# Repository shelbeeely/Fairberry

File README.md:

# Fairberry (e-ink fork)

This is a personal fork of [Dakkaron/Fairberry](https://github.com/Dakkaron/Fairberry), which adds a detachable BlackBerry Q10 keyboard to phones, physically clamped on and wired over USB. If you want that original phone-focused project, go there instead — this fork has moved away from it.

**The direction here now: a standalone, battery-powered BlackBerry-style device -- Q10 keyboard, a five-way trackball, a mic and speaker, microSD storage -- that pairs *wirelessly* with the [Xteink X4](https://www.xteink.com/products/xteink-x4) (or any BLE HID host) instead of physically attaching to it.** No separate battery / host-powered-only was the original project's whole philosophy; this fork has deliberately dropped that in favor of its own LiPo battery and its own enclosure, built primarily for e-ink devices running the [Free Ink SDK](https://freeink.org/) but not exclusive to them -- anything that speaks BLE HID keyboard is a valid target.

See [Hardware_Standalone_Smart_Keyboard.md](Documentation/Hardware_Standalone_Smart_Keyboard.md) for the current primary build. Two earlier, simpler stages are still in the repo and still valid if you want something less involved:
1. [Hardware_Fairberry_Mainboard.md](Documentation/Hardware_Fairberry_Mainboard.md) -- the original USB/BLE keyboard-only mainboard.
2. [Hardware_ESP32_Trackball_Mainboard.md](Documentation/Hardware_ESP32_Trackball_Mainboard.md) -- adds the trackball, still host-powered, classic ESP32.

The standalone smart keyboard supersedes both for pairing with the X4 specifically, but they're simpler builds if you don't want the battery/mic/speaker/SD/WiFi scope.

## Writer deck: four components, one repo

The keyboard alone is one half of the picture. Combined with an X4 running a FreeInk-SDK writer app, this becomes a full distraction-free writing device -- a "writer deck," in the vein of a Freewrite or AlphaSmart, built from this project's own parts. Four separate-but-interlinked pieces, all in this repo:

| Component | Directory | What it is |
|---|---|---|
| Keyboard firmware | [`BBQ10/`](BBQ10) | The physical keyboard + trackball + voice typing, BLE HID |
| X4 firmware | [`X4Firmware/`](X4Firmware) | The writer app (library + editor screens) running on the X4 |
| Hardware | [`KiCad/`](KiCad), [`Case/`](Case) | PCB design, 3D-printable case |
| Web GUI | [`WebGUI/`](WebGUI) | The keyboard-hosted local browser dashboard (implementation lives in `BBQ10/web_server.h`) |

Start with [Hardware_X4_Writer_Deck.md](Documentation/Hardware_X4_Writer_Deck.md) for how the pieces fit together -- it's also the most honestly unproven part of this repo (see its Status section: I read FreeInk SDK's docs site, but never had the actual SDK source or hardware in front of me to compile/test against, unlike the keyboard firmware).

## Status / known limitation

Good news on the software side: FreeInk SDK has a purpose-built BLE keyboard host — [`BleKeyboardHost`](https://freeink.org/docs/lib-ble) (the `lib-ble` library). Per its docs, it's a real BLE HID **host** (central role) that explicitly supports "keyboards, page turners, remote buttons and similar devices that expose the HID service" — not just page-turner remotes as I originally assumed here. It works on both ESP32-C3 and ESP32-S3 (BLE only, no Bluetooth Classic), which covers the plain X4 (C3) as well as the X4 Classic/Pro (S3). Pairing defaults to "Just Works" (no passkey needed), which is what a keyboard-only peripheral like Fairberry's `BOARD_TYPE ESP32` needs.

The catch: it's an **opt-in capability**, gated behind the `FREEINK_CAP_BLE_HID_HOST` build flag (off by default) plus adding the NimBLE stack as a dependency. So the real question isn't "does the ecosystem support external keyboards" (it does) — it's "does the specific firmware image flashed on your X4 have that flag turned on." Stock/vendor Xteink firmware almost certainly doesn't.

Checked directly against [freeink-sdk's `platformio.sample.ini`](https://github.com/Free-Ink/freeink-sdk/blob/main/platformio.sample.ini): the stock `[env:xteink_x4]` build env is just

```ini
[env:xteink_x4]
extends = base
board = esp32-c3-devkitm-1
build_flags =
  ${base.build_flags}
  -DFREEINK_DEVICE_X4=1
```

— no BLE HID host flag. Building a FreeInk-SDK firmware for the X4 that can actually pair with a Fairberry keyboard means adding, at minimum:

```ini
build_flags =
  ${base.build_flags}
  -DFREEINK_DEVICE_X4=1
  -DFREEINK_CAP_BLE_HID_HOST=1
lib_deps =
  ${base.lib_deps}
  h2zero/NimBLE-Arduino@^2.3.8
```

to your own build, then flashing that instead of whatever firmware is on the device now.

I have **not yet confirmed** this end-to-end against a physical X4 — that's the next step. I also haven't found documented USB HID host support in FreeInk SDK for any target, so the USB-attached Fairberry board types (`FAIRBERRY_V0_3_0`, `ARDUINO`) are more speculative than the BLE path right now; BLE (`BOARD_TYPE ESP32`) is the one with an actual matching host-side API to target.

## What can you expect?

Everything from the upstream project still applies at the electronics level: same BBQ10 keyboard, same mainboard, same firmware, same key combos (cursor mode, sticky modifiers, dead keys, backlight controls — see [UX_Shortcuts_and_Apps.md](Documentation/UX_Shortcuts_and_Apps.md)). What's changing here is the case/mount and the target device.

Demo video of the original phone version: 

## How to build it?

**Standalone smart keyboard (primary build)**: `BOARD_TYPE FAIRBERRY_ESP32S3_SMART` on an ESP32-S3. See [Hardware_Standalone_Smart_Keyboard.md](Documentation/Hardware_Standalone_Smart_Keyboard.md) for the pin plan, BOM (mic, speaker, microSD, LiPo + charger), firmware, and key combo table. Opt-in flags in `configuration.h`: `TRACKBALL_ENABLED`, `AUDIO_ENABLED` (local recording/playback, fully offline), `WIFI_TRANSCRIPTION_ENABLED` (batch-syncs recordings to the OpenAI Whisper API), `TRANSFER_MODE_ENABLED` (local no-cloud web dashboard for browsing/downloading notes over LAN), `VOICE_TYPING_ENABLED` (immediate dictate -> hear it read back via TTS to verify -> Enter to send, like a phone's voice-to-text keyboard). The last three need `BBQ10/secrets.h` -- copy `secrets.h.example`. No enclosure design yet -- see that doc's Enclosure section for why. **None of this is validated against real hardware.**

**Simpler builds**, if you don't want the battery/audio/WiFi scope:
- [Custom mainboard](Documentation/Hardware_Fairberry_Mainboard.md) — `BOARD_TYPE FAIRBERRY_V0_3_0` (USB) or `BOARD_TYPE ESP32` (BLE), keyboard only.
- [+ trackball](Documentation/Hardware_ESP32_Trackball_Mainboard.md) — same `BOARD_TYPE ESP32`, adds `TRACKBALL_ENABLED`.
- [Old Arduino-based hardware](Documentation/Hardware_Arduinobased.md) also still works.

For these simpler, host-attached builds only (not the standalone smart keyboard, which has no case yet), there's a case preset: [Xteink X4 preset](Case/Generator/presets/XteinkX4.scad), built from width/thickness measured off a community-made, to-scale device model ([Zorian22's "Xteink X4 device model" on Thingiverse](https://www.thingiverse.com/thing:7287950), 114.2 x 69.2 x 6.2mm) rather than just the rounded marketing spec — better, but still not a full match to the real device shape. The preset file has step-by-step instructions for swapping in that actual dummy model file for a proper fit instead of the parametric approximation; I couldn't fetch it automatically since Thingiverse's terms block bots, so that step needs a normal browser download on your end. Print a bottom-only test fit before committing to a full case either way. The original phone presets (Fairphone 4, Samsung Galaxy A54) are still in the repo under `Case/Generator/presets/` for reference.

**Writer deck combined case**: [Case/WriterDeck/](Case/WriterDeck) -- a single clamshell enclosing both the keyboard and the X4 as one physical device, reusing a real interlocking hinge mechanism extracted from a user-provided reference model rather than designed from scratch. First-draft OpenSCAD, not print-tested -- see that directory's README for exactly what's confirmed-real (the hinge geometry, the keyboard module dimensions) versus still a placeholder (tray cavity depth, trackball position).

## How to use it?

[Key combinations and apps](Documentation/UX_Shortcuts_and_Apps.md)

## License

Same as upstream: [Attribution-NonCommercial-ShareAlike 4.0 International](https://creativecommons.org/licenses/by-nc-sa/4.0/) for the firmware and case files (see individual file headers), original work © Dakkaron.

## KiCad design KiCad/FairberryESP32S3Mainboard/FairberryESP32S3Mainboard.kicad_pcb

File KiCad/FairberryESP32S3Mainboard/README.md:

# FairberryESP32S3Mainboard

KiCad 7 schematic for the standalone smart-keyboard mainboard (ESP32-S3-WROOM-1,
trackball, mic, speaker amp, microSD, LiPo charger). Pin assignments match
`BBQ10/boards.h`'s `FAIRBERRY_ESP32S3_SMART` board type exactly.

31 components, 44 verified nets (every net has 2+ pins, no dangling nets).
Connectivity uses net labels (`(label "NETNAME" ...)`) on short wire stubs at
each pin rather than routed point-to-point wires, which is standard KiCad
practice for pin-dense boards and keeps the sheet readable.

This is the schematic only -- `FairberryESP32S3Mainboard.kicad_pcb` exists
(see PCB section below) but only has the netlist imported: footprints sit on
an unplaced grid with no board outline or routing yet. `FairberryESP32S3Mainboard.svg`
is exported straight from the `.kicad_sch` via `kicad-cli sch export svg`
(see the command below); if you change the schematic, regenerate it the
same way so the image doesn't go stale:

```sh
export KICAD7_SYMBOL_DIR=/usr/share/kicad/symbols
xvfb-run -a kicad-cli sch export svg FairberryESP32S3Mainboard.kicad_sch -o /tmp/out
cp /tmp/out/FairberryESP32S3Mainboard.svg FairberryESP32S3Mainboard.svg
```

## Module SKU: ESP32-S3-WROOM-1-N16R8

The schematic symbol (`RF_Module:ESP32-S3-WROOM-1`) is generic across every
WROOM-1 flash/PSRAM SKU — the pinout is identical. For the BOM, this board
specs the **-N16R8** variant (16MB flash, 8MB octal PSRAM) for headroom on
audio buffers, the web dashboard, and WiFi/TLS.

That choice has one real consequence: on any *octal*-PSRAM WROOM-1 SKU
(anything ending `R8` or `R16V`), GPIO35/36/37 are wired internally to the
in-package PSRAM and can't be used as GPIO — they simply don't work as
signal pins, even though the generic symbol still draws them. A cheaper
*quad*-PSRAM SKU (`R2`, e.g. -N16R2, 2MB PSRAM) wouldn't have this
restriction and would need no pin changes, at the cost of much less RAM.
Having picked -N16R8, mic I2S was moved off GPIO35-37 onto GPIO43/44
(silkscreened RXD0/TXD0, i.e. UART0 — free because this board's console
runs over native USB, not UART0) and GPIO46 (a strapping pin, safe here
since MIC_DIN is an input and the mic's output doesn't drive that pin
during a bootloader-mode reset). See the comment above
`MIC_I2S_WS_PIN` in `BBQ10/boards.h` for the full reasoning.

## Known simplifications (not yet fab-ready)

- **J6 (USB)**: a plain 4-pin header standing in for a real USB-C receptacle.
  No CC1/CC2 pull-down resistors are present, so USB-C power negotiation
  won't work as-is — replace with a real USB-C connector symbol/footprint
  (with CC resistors) before fabrication.
- **U3 (3.3V LDO)**: uses the generic `Regulator_Linear:MCP1700x-300xxTT`
  base symbol (the `extends`-based `-330` variant wasn't practical to
  reference programmatically); functionally equivalent, same pinout.
- **U6 (battery-low supervisor)**: uses the generic
  `Power_Supervisor:MCP100-270D` base symbol; the real BOM part is the
  -300 (3.0V threshold) variant, same pinout.
- **U4 (MAX98357A)**: footprint is the QFN package; double-check against
  the actual part you source (some breakout modules differ).

## Regenerating the schematic

The `.kicad_sch` file is generated, not hand-drawn, from `generator/*.py`
(pulls real symbol/pin data straight out of the installed `kicad-symbols`
library files, plus a hand-built symbol for the BBQ10 keyboard's Hirose
connector sourced from `KiCad/FairberryMainboard/library/Keyboard.lib`).
To regenerate after editing `generator/build_sch3.py` (component list /
net map):

```sh
cd KiCad/FairberryESP32S3Mainboard/generator
python3 build_sch4.py
```

This overwrites `../FairberryESP32S3Mainboard.kicad_sch` and prints every
net with its pin list, plus a warning for any single-pin (dangling) net.

## Generating the PCB

`kicad-cli`'s `pcb` subcommand only has `export` in KiCad 7 -- there's no
`pcb import-netlist`, and the GUI's "Update PCB from Schematic" dialog
isn't exposed to scripting either. `generator/build_pcb.py` does that step
directly against the `pcbnew` Python API instead: it loads each
component's real footprint (verifying every one exists on disk -- one
placeholder footprint name and one wrong library path were caught and
fixed this way, see `build_sch3.py`'s `FP` dict comments), places them on
an unrouted grid, and wires every pad to its net by pad *number* (cross-checked
against each real `.kicad_mod` file, not assumed to equal the schematic
pin number sight unseen -- e.g. the microSD footprint's shield pin is 4
physical pads that all share pad number 9, matched by grouping pads by
number rather than taking the first hit).

```sh
cd KiCad/FairberryESP32S3Mainboard/generator
python3 build_pcb.py
```

This overwrites `../FairberryESP32S3Mainboard.kicad_pcb` and prints the
footprint/net counts. It needs `pcbnew` (KiCad's Python bindings,
`/usr/lib/python3/dist-packages/pcbnew.py` + `_pcbnew.so` on this
environment's install) importable from plain `python3` — no
`KICAD7_SYMBOL_DIR` or `xvfb` needed for this step, those only matter for
`kicad-cli`.

**Not done yet:** board outline, footprint placement (beyond "doesn't
overlap"), and routing. Placement/outline depend on the case's real
dimensions; routing is real layout work on top of this.

## Verifying with kicad-cli

`kicad-cli` (KiCad 7) needs `KICAD7_SYMBOL_DIR` set (the environment this was
built in didn't have it set by default) and a display, even for headless
export (it's a wx/GTK app under the hood) — use `xvfb-run` if there's no X
server:

```sh
export KICAD7_SYMBOL_DIR=/usr/share/kicad/symbols
cd KiCad/FairberryESP32S3Mainboard
xvfb-run -a kicad-cli sch export svg FairberryESP32S3Mainboard.kicad_sch -o /tmp/out
xvfb-run -a kicad-cli sch export netlist FairberryESP32S3Mainboard.kicad_sch -o /tmp/out.net
```

Then sanity-check the netlist: every net should have 2+ nodes except a
short, expected list of no-connects (unused ESP32-S3 strapping pins
IO0/IO3/IO45, the octal-PSRAM-reserved IO35/36/37 (see the Module SKU
section — RXD0/TXD0 aren't in this list anymore, they carry mic I2S now),
MAX98357A's NC pins, and J1's MIC pin from the keyboard connector, which
isn't used since a separate mic — U5 — is on this board).

To check the same thing on the PCB instead of the schematic (useful after
running `build_pcb.py`, to confirm every pad landed on the net it should
have):

```sh
python3 -c "
import pcbnew
board = pcbnew.LoadBoard('FairberryESP32S3Mainboard.kicad_pcb')
netpads = {}
for fp in board.GetFootprints():
    for pad in fp.Pads():
        netpads.setdefault(pad.GetNetname(), 0)
        netpads[pad.GetNetname()] += 1
single = [n for n, c in netpads.items() if c == 1 and n]
print('single-pad (dangling) nets:', single or 'none')
"
```

A PCB-only rendering (copper + silkscreen + outline, no schematic-style
labels) can be exported the same way as the schematic, except `-o` here
takes a file path directly rather than a directory when `--layers` is
given:

```sh
xvfb-run -a kicad-cli pcb export svg FairberryESP32S3Mainboard.kicad_pcb -o /tmp/out.svg --layers F.Cu,F.Silkscreen,Edge.Cuts
```

### Pitfalls hit building this (kept here so they don't get re-debugged)

- **kicad-cli segfaults** on any schematic referencing a real library
  symbol if `KICAD7_SYMBOL_DIR` is unset or there's no local/global
  `sym-lib-table` — but it *also* segfaults on a well-formed file if a
  symbol's cached name in `lib_symbols` doesn't exactly match its `lib_id`
  (e.g. a `Heater` block cached for something referenced as `Device:R`).
  Getting a clean `Failed to load schematic file` instead of a segfault
  means the structural error is at least being caught.
- **`(wire ...)` must not include a `(fill (type none))` clause** and
  should use `(type solid)`, not `(type default)` — copying the stroke
  syntax from a symbol's graphic *rectangle* onto a wire breaks loading.
- **Pin connection points must be exact, unrounded coordinates.** Snapping
  a computed pin position to the nearest 1.27mm grid before drawing its
  wire stub seems harmless but silently detaches the wire from the pin
  whenever the component's placement position isn't itself grid-aligned —
  the file still loads and renders fine, wires visually touch the pins,
  but `kicad-cli sch export netlist` shows almost everything as
  "unconnected". Always compute `component_position + pin_local_offset`
  with no rounding for the pin end of any wire.
- **A schematic's `Footprint` property string is never validated against
  real files.** The microSD footprint (`Connector_Card:Conn_01x08_MicroSD_Card`)
  was a guessed name that doesn't exist in KiCad's footprint library, and
  the custom keyboard connector's footprint was referenced under a made-up
  `Fairberry:` library instead of the real `Connectors_Hirose_extra:` one
  it actually lives in — both loaded fine as schematic text and only broke
  when `build_pcb.py` called `pcbnew.FootprintLoad()` on them and got
  `None`. Nothing catches a bad footprint string until PCB generation.
- **Footprint pads can outnumber symbol pins**, and pad *numbers* -- not
  symbol pin numbers assumed to carry over unchanged -- are what has to
  match. The microSD footprint has 4 physical shield pads that all share
  pad number 9, corresponding to the symbol's single SHIELD pin; grouping
  a footprint's pads by `GetNumber()` before assigning nets (rather than
  taking the first match, or assuming a 1:1 pad-to-pin count) is what
  catches this.

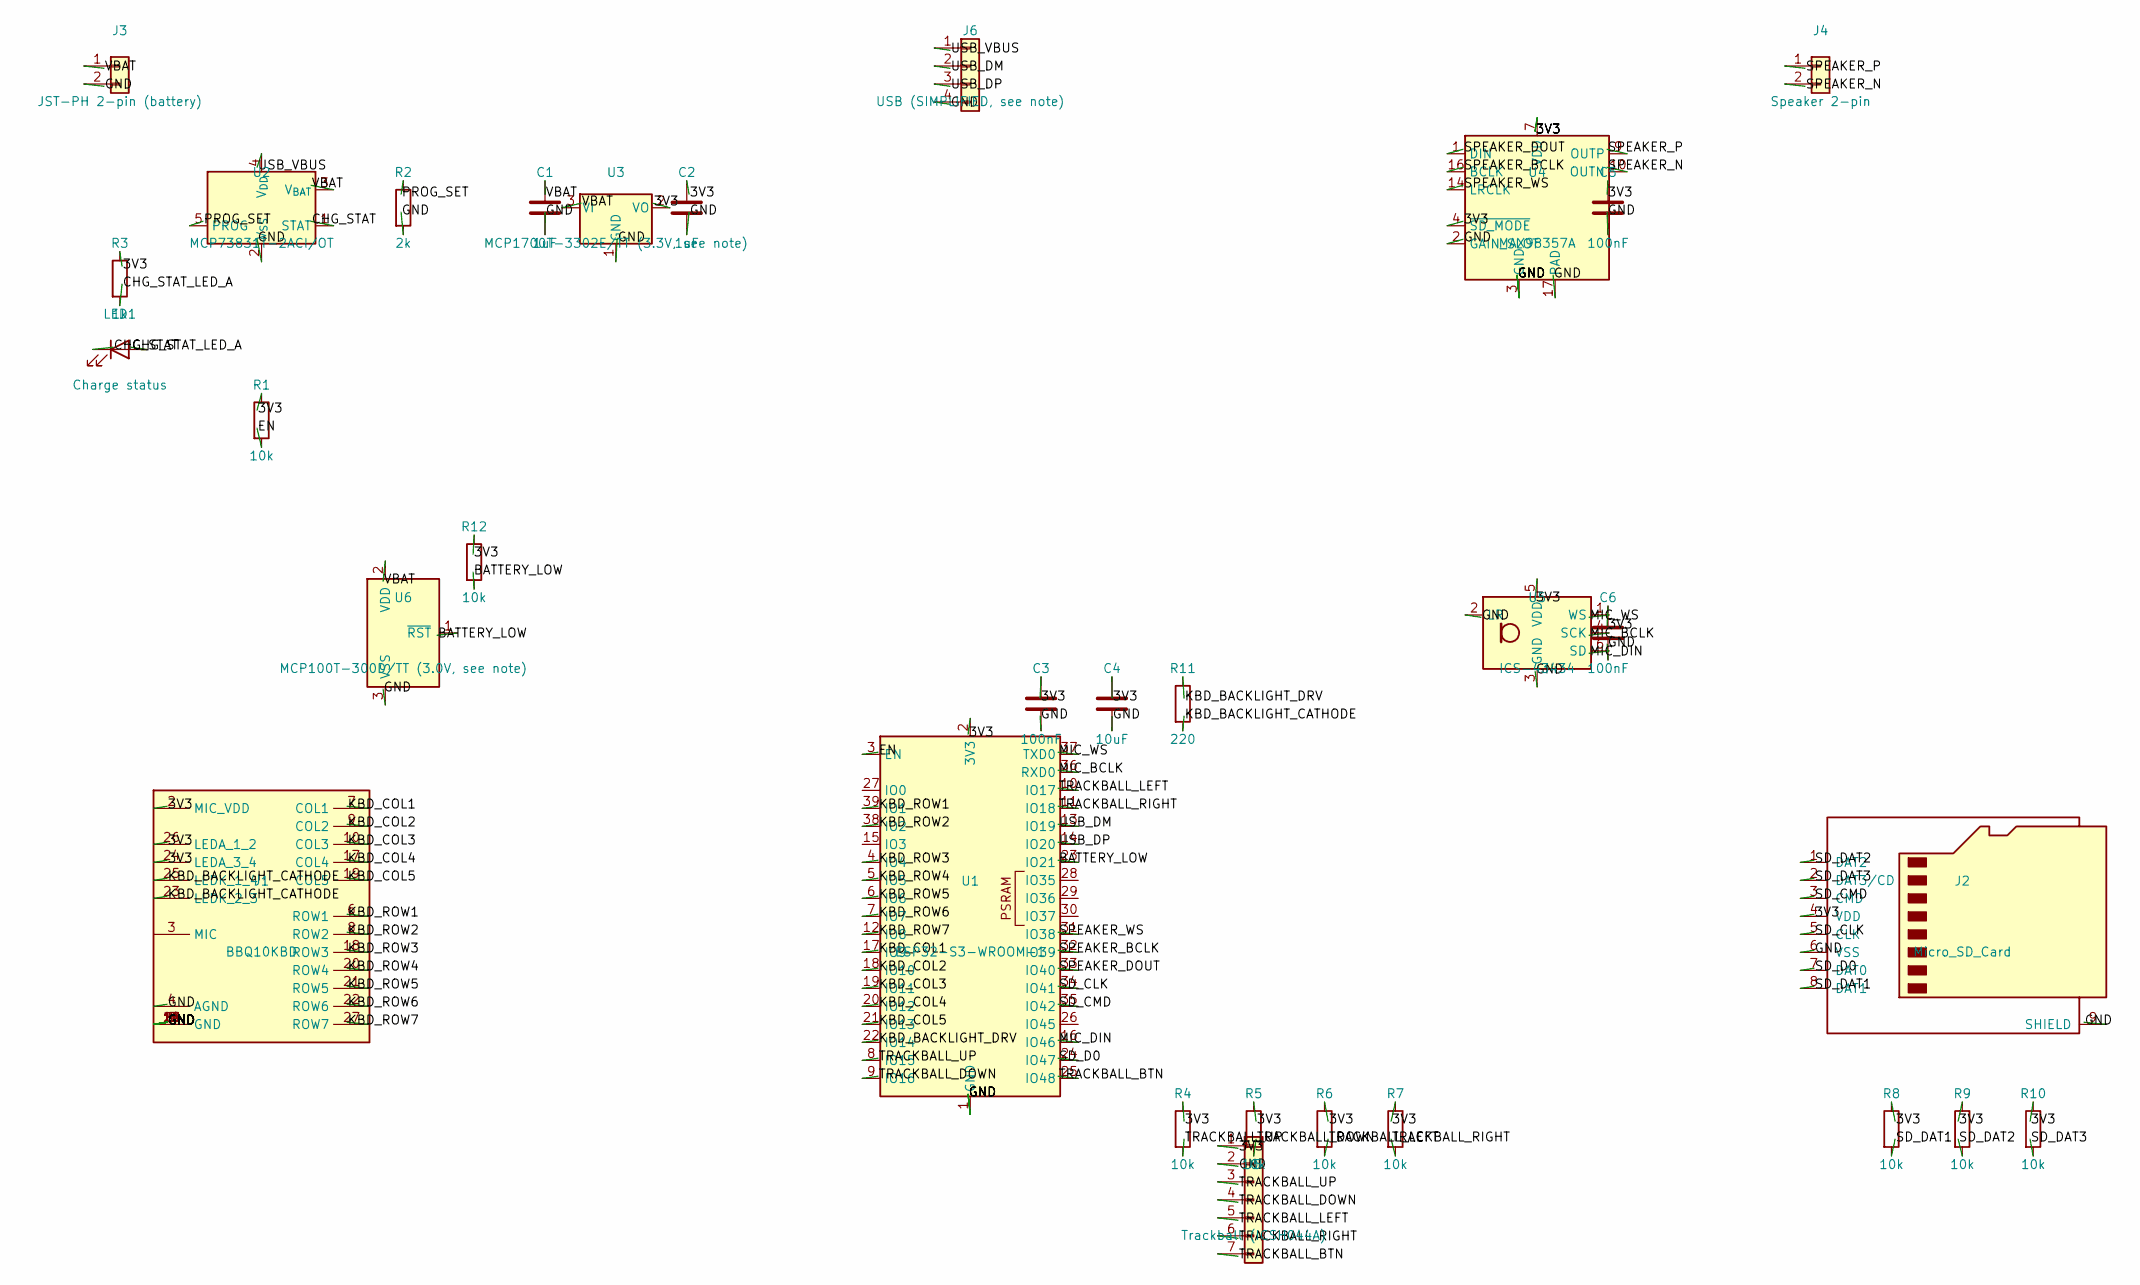
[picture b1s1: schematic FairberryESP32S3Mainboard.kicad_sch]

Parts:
C1, C2: 1uF; C_0603_1608Metric
C3, C5, C6: 100nF; C_0603_1608Metric
C4: 10uF; C_0603_1608Metric
J1: BBQ10KBD; BM14B(0.8)-24DS-0.4V(53)
J2: Micro_SD_Card; microSD_HC_Wuerth_693072010801
J3: JST-PH 2-pin (battery); PinHeader_1x02_P2.54mm_Vertical
J4: Speaker 2-pin; PinHeader_1x02_P2.54mm_Vertical
J5: Trackball (ICSH044A); PinHeader_1x07_P2.54mm_Vertical
J6: USB (SIMPLIFIED, see note); PinHeader_1x04_P2.54mm_Vertical
LED1: Charge status; LED_0603_1608Metric
R1, R4, R5, R6, R7, R8, R9, R10, R12: 10k; R_0603_1608Metric
R2: 2k; R_0603_1608Metric
R3: 1k; R_0603_1608Metric
R11: 220; R_0603_1608Metric
U1: ESP32-S3-WROOM-1
U2: MCP73831T-2ACI/OT; SOT-23-5
U3: MCP1700T-3302E/TT (3.3V, see note); SOT-23
U4: MAX98357A; TQFN-16-1EP_3x3mm_P0.5mm_EP1.23x1.23mm
U5: ICS-43434; InvenSense_ICS-43434-6_3.5x2.65mm
U6: MCP100T-300D/TT (3.0V, see note); SOT-23-3

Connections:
3V3: C2.1, C3.1, C4.1, C5.1, C6.1, J1.2 (MIC_VDD), J1.24 (LEDA_3_4), J1.26 (LEDA_1_2), J2.4 (VDD), J5.1, R1.1, R3.1, R4.1, R5.1, R6.1, R7.1, R8.1, R9.1, R10.1, R12.1, U1.2 (3V3), U3.2 (VO), U4.4 (~SD_MODE), U4.7 (VDD), U4.8 (VDD), U5.5 (VDD)
BATTERY_LOW: R12.2, U1.23 (IO21), U6.1 (~RST)
CHG_STAT: LED1.1 (K), U2.1 (STAT)
CHG_STAT_LED_A: LED1.2 (A), R3.2
EN: R1.2, U1.3 (EN)
GND: C1.2, C2.2, C3.2, C4.2, C5.2, C6.2, J1.1 (GND), J1.4 (AGND), J1.5 (GND), J1.11 (GND), J1.12 (GND), J1.13 (GND), J1.14 (GND), J1.15 (GND), J1.16 (GND), J1.28 (GND), J2.6 (VSS), J2.9 (SHIELD), J3.2, J5.2, J6.4, R2.2, U1.1 (GND), U1.40 (GND), U1.41 (GND), U2.2 (V_{SS}), U3.1 (GND), U4.2 (GAIN_SLOT), U4.3 (GND), U4.11 (GND), U4.15 (GND), U4.17 (PAD), U5.2 (LR), U5.3 (GND), U6.3 (VSS)
KBD_BACKLIGHT_CATHODE: J1.23 (LEDK_2_3), J1.25 (LEDK_1_4), R11.2
KBD_BACKLIGHT_DRV: R11.1, U1.22 (IO14)
KBD_COL1: J1.7 (COL1), U1.17 (IO9)
KBD_COL2: J1.9 (COL2), U1.18 (IO10)
KBD_COL3: J1.10 (COL3), U1.19 (IO11)
KBD_COL4: J1.17 (COL4), U1.20 (IO12)
KBD_COL5: J1.19 (COL5), U1.21 (IO13)
KBD_ROW1: J1.6 (ROW1), U1.39 (IO1)
KBD_ROW2: J1.8 (ROW2), U1.38 (IO2)
KBD_ROW3: J1.18 (ROW3), U1.4 (IO4)
KBD_ROW4: J1.20 (ROW4), U1.5 (IO5)
KBD_ROW5: J1.21 (ROW5), U1.6 (IO6)
KBD_ROW6: J1.22 (ROW6), U1.7 (IO7)
KBD_ROW7: J1.27 (ROW7), U1.12 (IO8)
MIC_BCLK: U1.36 (RXD0), U5.4 (SCK)
MIC_DIN: U1.16 (IO46), U5.6 (SD)
MIC_WS: U1.37 (TXD0), U5.1 (WS)
PROG_SET: R2.1, U2.5 (PROG)
SD_CLK: J2.5 (CLK), U1.34 (IO41)
SD_CMD: J2.3 (CMD), U1.35 (IO42)
SD_D0: J2.7 (DAT0), U1.24 (IO47)
SD_DAT1: J2.8 (DAT1), R8.2
SD_DAT2: J2.1 (DAT2), R9.2
SD_DAT3: J2.2 (DAT3/CD), R10.2
SPEAKER_BCLK: U1.32 (IO39), U4.16 (BCLK)
SPEAKER_DOUT: U1.33 (IO40), U4.1 (DIN)
SPEAKER_N: J4.2, U4.10 (OUTN)
SPEAKER_P: J4.1, U4.9 (OUTP)
SPEAKER_WS: U1.31 (IO38), U4.14 (LRCLK)
TRACKBALL_BTN: J5.7, U1.25 (IO48)
TRACKBALL_DOWN: J5.4, R5.2, U1.9 (IO16)
TRACKBALL_LEFT: J5.5, R6.2, U1.10 (IO17)
TRACKBALL_RIGHT: J5.6, R7.2, U1.11 (IO18)
TRACKBALL_UP: J5.3, R4.2, U1.8 (IO15)
USB_DM: J6.2, U1.13 (IO19)
USB_DP: J6.3, U1.14 (IO20)
USB_VBUS: J6.1, U2.4 (V_{DD})
VBAT: C1.1, J3.1, U2.3 (V_{BAT}), U3.3 (VI), U6.2 (VDD)

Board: 2 copper layers, 31 parts (0 on the bottom side), 44 nets, no tracks yet.

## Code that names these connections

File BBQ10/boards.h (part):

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  // external pull-up resistor to 3.3V per line (see the hardware doc).
  // BTN uses a normal pin with the ESP32's internal pull-up instead,
  // since only 4 input-only pins exist and BTN was the 5th line.
  #define TRACKBALL_UP_PIN 34
  #define TRACKBALL_DOWN_PIN 36
  #define TRACKBALL_LEFT_PIN 39
  #define TRACKBALL_RIGHT_PIN 35
  #define TRACKBALL_BTN_PIN 14

  // LEDs are optional (TRACKBALL_LED_ENABLED). WHT isn't wired up here --
  // it wasn't needed for a functional trackball and there wasn't a 4th
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  // all normal bidirectional pins -- no input-only pins forced onto the
  // direction lines here, though external pull-ups are still recommended
  // per the trackball doc's sensor-polarity caveat.
  #define TRACKBALL_UP_PIN 15
  #define TRACKBALL_DOWN_PIN 16
  #define TRACKBALL_LEFT_PIN 17
  #define TRACKBALL_RIGHT_PIN 18
  // Not a deep-sleep wake source in this revision -- GPIO48 isn't
  // RTC-capable, unlike the pin used in the earlier draft. Doubling BTN
  // as the wake button would need it moved back into the 0-21 RTC-capable
  // range, trading away whatever else was there; not done here since
  // there's no spare pin to trade with. A dedicated wake button (or deep
  // sleep entirely via power switch) is open follow-up work.
  #define TRACKBALL_BTN_PIN 48

  // RGB LEDs cut from this revision -- no pins left after fixing the
  // GPIO22-25/33-34 mistake above. TRACKBALL_LED_ENABLED will fail to
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  // the "know the battery percentage" goal in the BOM doc, not a free
  // substitution. A fuel gauge over I2C would restore percentage-level
  // monitoring in a follow-up revision without costing a pin.
  #define BATTERY_LOW_PIN 21

  // Mic (I2S MEMS mic, e.g. ICS-43434 -- see the KiCad schematic; more
  // readily available with a real KiCad symbol than the INMP441
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  // N16R8) -- so mic I2S can't live there like an earlier draft of this
  // board had it. It's moved onto GPIO43/44 (silkscreened RXD0/TXD0,
  // i.e. UART0) instead, which cost nothing: this board's serial
  // console/flashing already goes over native USB (GPIO19/20, USB_DM/DP),
  // not UART0, so those two pins were unused. The third pin (DIN, an
  // input) goes on GPIO46 -- a strapping pin, but safe for this because
  // it only matters as an input during a bootloader-mode reset, and the
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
